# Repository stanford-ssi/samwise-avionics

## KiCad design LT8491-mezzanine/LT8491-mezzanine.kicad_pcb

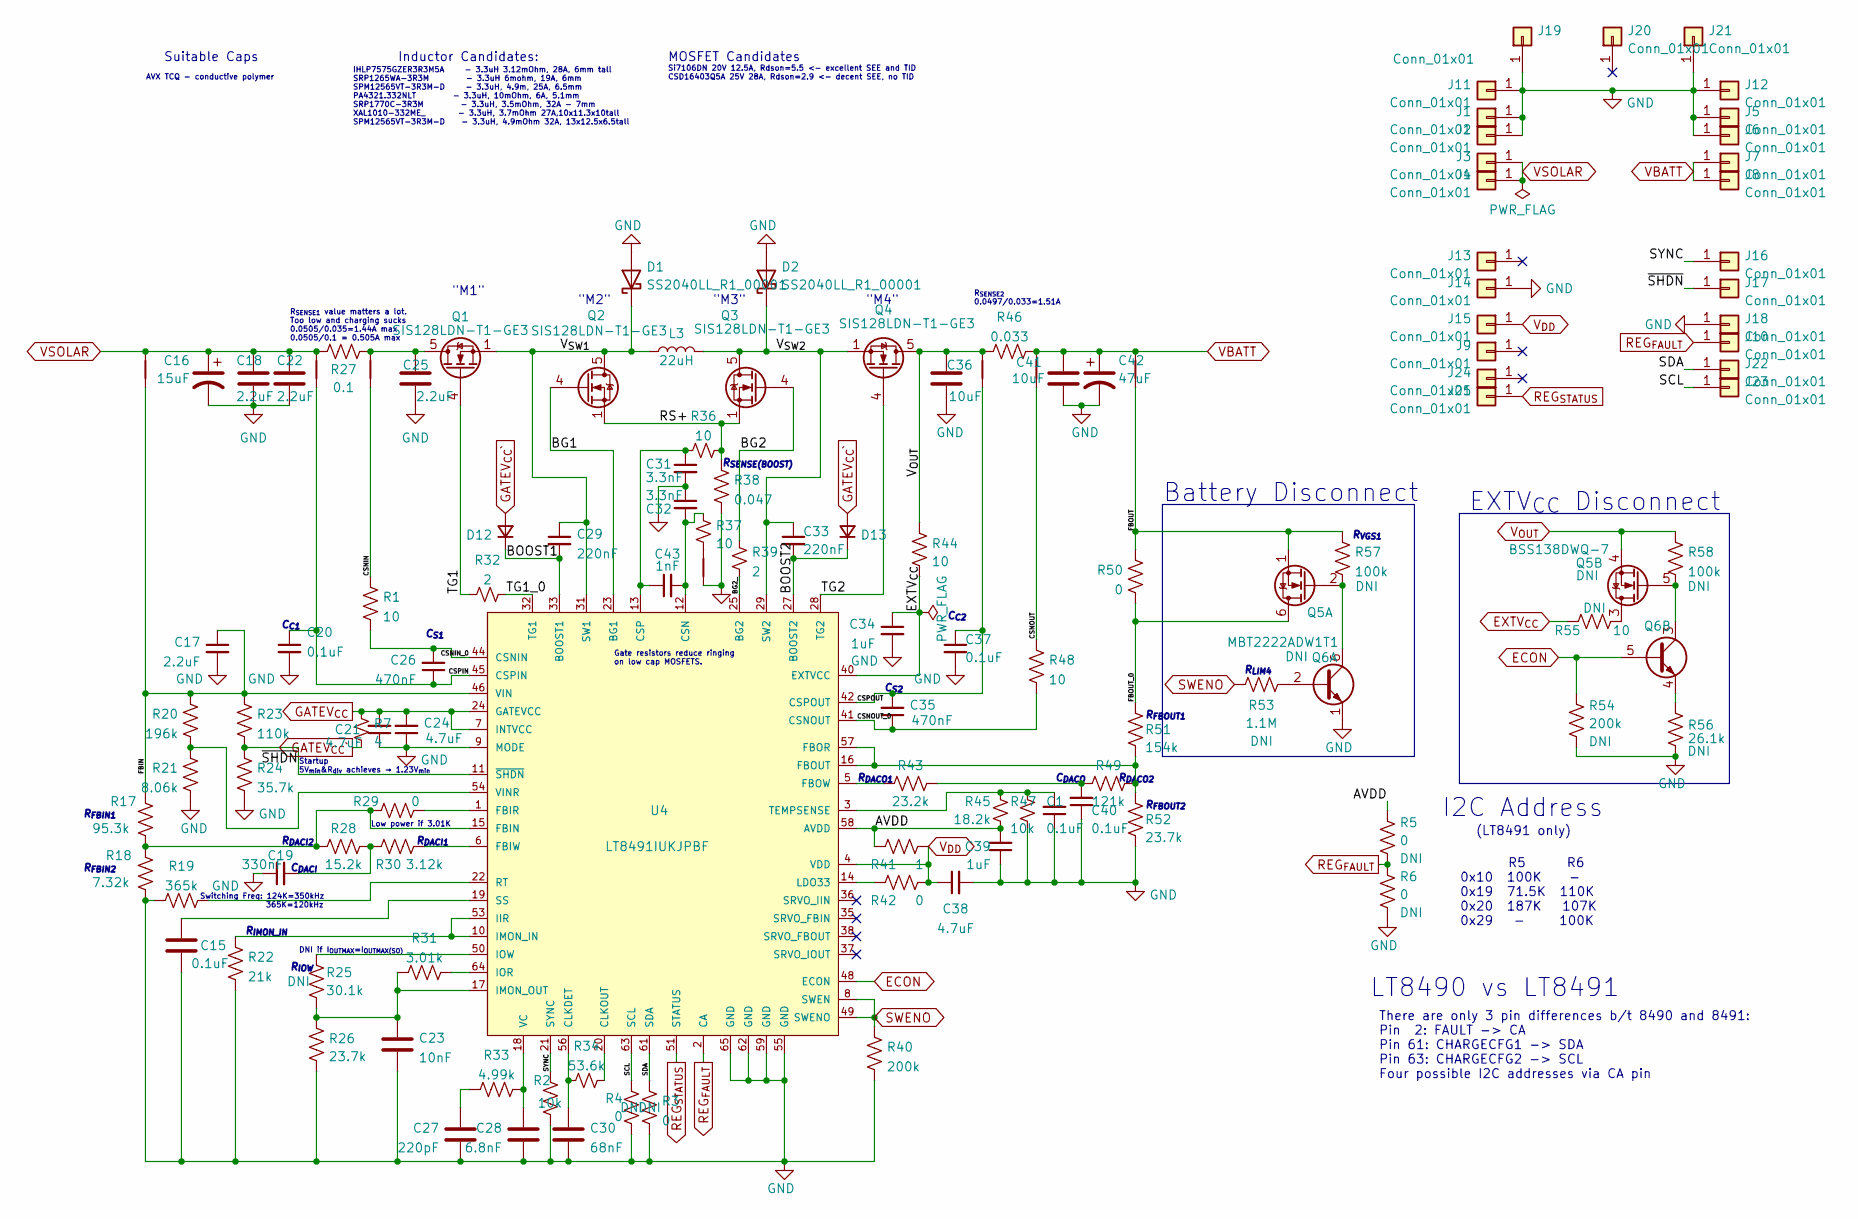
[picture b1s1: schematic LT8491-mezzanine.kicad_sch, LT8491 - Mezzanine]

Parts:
C1, C15, C20, C37, C40: 0.1uF; C_0603_1608Metric
C16: 15uF; CP_EIA-7343-30_AVX-N; Voltage 75V; Manufacturer_Part_Number TCQD336M016R0070E
C17, C18, C22, C25: 2.2uF; C_0805_2012Metric
C19: 330nF; C_0603_1608Metric
C21, C24, C38: 4.7uF; C_0603_1608Metric
C23: 10nF; C_0603_1608Metric
C26, C35: 470nF; C_0603_1608Metric
C27: 220pF; C_0603_1608Metric
C28: 6.8nF; C_0603_1608Metric
C29, C33: 220nF; C_0603_1608Metric
C30: 68nF; C_0603_1608Metric
C31, C32: 3.3nF; C_0603_1608Metric
C34, C39: 1uF; C_0603_1608Metric
C36, C41: 10uF; C_0805_2012Metric
C42: 47uF; CP_EIA-7343-30_AVX-N; Voltage 16V; Manufacturer_Part_Number TCQD476M016R0070E
C43: 1nF; C_0603_1608Metric
D1, D2: SS2040LL_R1_00001; D_PowerDI-123
D12, D13: CMMR1U-02 TR; D_SOD-123F
J1, J2, J3, J4, J5, J6, J7, J8, J9, J10, J11, J12, J13, J14, J15, J16, J17, J18, J19, J20, J21, J22, J23, J24, J25: Conn_01x01; mppt_castellation_05mm
L3: 22uH; L_SRP1770CC
NT1, NT2, NT3, NT4, NT5, NT6, NT7: NetTie_2; NetTie-2_SMD_Pad0.5mm
Q1, Q2, Q3, Q4: SIS128LDN-T1-GE3; Manufacturer_Part_Number SIS128LDN-T1-GE3
Q5: BSS138DWQ-7; Manufacturer_Part_Number BSS138DWQ-7; Mouser Part Number 621-BSS138DWQ-7
Q6: MBT2222ADW1T1; SOT-363_SC-70-6; Manufacturer_Part_Number MBT2222ADW1T1
R1, R36, R37, R44, R48, R55: 10; R_0603_1608Metric
R2, R47: 10k; R_0603_1608Metric
R3, R4, R5, R6, R29, R42, R50: 0; R_0603_1608Metric
R7: 4; R_0603_1608Metric
R17: 95.3k; R_0603_1608Metric
R18: 7.32k; R_0603_1608Metric
R19: 365k; R_0603_1608Metric
R20: 196k; R_0603_1608Metric
R21: 8.06k; R_0603_1608Metric
R22: 21k; R_0603_1608Metric
R23: 110k; R_0603_1608Metric
R24: 35.7k; R_0603_1608Metric
R25: 30.1k; R_0603_1608Metric
R26, R52: 23.7k; R_0603_1608Metric
R27: 0.1; R_1206_3216Metric
R28: 15.2k; R_0603_1608Metric
R30: 3.12k; R_0603_1608Metric
R31: 3.01k; R_0603_1608Metric
R32, R39: 2; R_0603_1608Metric
R33: 4.99k; R_0603_1608Metric
R34: 53.6k; R_0603_1608Metric
R38: 0.047; R_1206_3216Metric
R40, R54: 200k; R_0603_1608Metric
R41: 1; R_0603_1608Metric
R43: 23.2k; R_0603_1608Metric
R45: 18.2k; R_0603_1608Metric
R46: 0.033; R_1206_3216Metric
R49: 121k; R_0603_1608Metric
R51: 154k; R_0603_1608Metric
R53: 1.1M; R_0603_1608Metric
R56: 26.1k; R_0603_1608Metric
R57, R58: 100k; R_0603_1608Metric
U4: LT8491IUKJPBF; LT8491IUKJ#PBF

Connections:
/AVDD: C39.2, R5.1, R41.2, R45.2, U4.58 (AVDD)
/BG1: Q2.4 (G), U4.23 (BG1)
/BG2: Q3.4 (G), R39.1
/BG2_: R39.2, U4.25 (BG2)
/BOOST1: C29.2, D12.1 (K), U4.33 (BOOST1)
/BOOST2: C33.2, D13.1 (K), U4.27 (BOOST2)
/CSNIN: NT3.1, R1.1
/CSNIN_0: C26.2, R1.2, U4.44 (CSNIN)
/CSNOUT: NT5.1, R48.1
/CSNOUT_0: C35.1, R48.2, U4.41 (CSNOUT)
/CSPIN: C20.1, C26.1, NT2.1, U4.45 (CSPIN)
/CSPOUT: C35.2, C37.1, NT4.1, U4.42 (CSPOUT)
/EXTV_{CC}: C34.1, R44.2, R55.2, U4.40 (EXTVCC)
/FBIN: C17.1, NT6.1, R17.1, R20.1, R23.1, U4.46 (VIN)
/FBOUT: NT7.1, Q5.1 (S2), R50.1, R57.2
/FBOUT_0: Q5.6 (D1), R50.2, R51.1
/RS+: Q2.1 (S), Q2.2 (S), Q2.3 (S), Q3.1 (S), Q3.2 (S), Q3.3 (S), R36.1, R38.1
/SCL: J23.1, R4.1, U4.63 (SCL)
/SDA: J22.1, R3.1, U4.61 (SDA)
/SYNC: J16.1, R2.1, U4.21 (SYNC)
/TG1: Q1.4 (G), R32.2
/TG1_0: R32.1, U4.32 (TG1)
/TG2: Q4.4 (G), U4.28 (TG2)
/V_{OUT}: C36.1, NT4.2, Q4.5 (D), Q5.4 (S1), R44.1, R46.1, R58.2
/V_{SW1}: C29.1, D1.1 (K), L3.1, Q1.1 (S), Q1.2 (S), Q1.3 (S), Q2.5 (D), U4.31 (SW1)
/V_{SW2}: C33.1, D2.1 (K), L3.2, Q3.5 (D), Q4.1 (S), Q4.2 (S), Q4.3 (S), U4.29 (SW2)
/~SHDN: J17.1, R23.2, R24.1, U4.11 (~SHDN)
ECON: Q6.5 (B2), R54.1, U4.48 (ECON)
GATEV_{CC}: C21.2, C24.2, R7.2, U4.7 (INTVCC), U4.24 (GATEVCC)
GATEV_{CC}`: D12.2 (A), D13.2 (A), R7.1
GND: C1.1, C15.2, C16.2, C17.2, C18.2, C19.1, C20.2, C21.1, C22.2, C23.2, C24.1, C25.2, C27.2, C28.1, C30.2, C31.2, C32.1, C34.2, C36.2, C37.2, C38.2, C39.1, C40.1, C41.2, C42.2, D1.2 (A), D2.2 (A), J1.1, J2.1, J5.1, J6.1, J11.1, J12.1, J14.1, J18.1, J19.1, J21.1, NT1.1, Q6.1 (E1), R2.2, R3.2, R4.2, R6.2, R18.2, R19.2, R21.2, R22.2, R24.2, R26.2, R38.2, R40.2, R47.1, R52.2, R54.2, R56.1, U4.9 (MODE), U4.55 (GND), U4.59 (GND), U4.62 (GND), U4.65 (GND)
unnamed: C19.2, R28.1, R30.2
unnamed: C27.1, R33.1
unnamed: C40.2, R43.1, R49.2
unnamed: NT1.2, R37.2
unnamed: C25.1, NT3.2, Q1.5 (D), R27.2
unnamed: Q5.2 (G2), Q6.6 (C1), R57.1
unnamed: Q5.3 (D2), R55.1
unnamed: Q5.5 (G1), Q6.3 (C2), R58.1
unnamed: Q6.2 (B1), R53.2
unnamed: Q6.4 (E2), R56.2
unnamed: C30.1, R34.1, U4.56 (CLKDET)
unnamed: R34.2, U4.20 (CLKOUT)
unnamed: C32.2, C43.2, R37.1, U4.12 (CSN)
unnamed: C31.1, C43.1, R36.2, U4.13 (CSP)
unnamed: R17.2, R18.1, R28.2, R29.2, U4.15 (FBIN)
unnamed: R29.1, U4.1 (FBIR)
unnamed: R30.1, U4.6 (FBIW)
unnamed: R49.1, R51.2, R52.1, U4.16 (FBOUT), U4.57 (FBOR)
unnamed: R43.2, U4.5 (FBOW)
unnamed: R22.1, U4.10 (IMON_IN), U4.53 (IIR)
unnamed: C23.1, R25.2, R26.1, R31.2, U4.17 (IMON_OUT)
unnamed: R31.1, U4.64 (IOR)
unnamed: R25.1, U4.50 (IOW)
unnamed: R42.2, U4.14 (LDO33)
unnamed: R19.1, U4.22 (RT)
unnamed: C15.1, U4.19 (SS)
unnamed: C1.2, R45.1, R47.2, U4.3 (TEMPSENSE)
unnamed: C28.2, R33.2, U4.18 (VC)
unnamed: R20.2, R21.1, U4.54 (VINR)
REG_{FAULT}: J10.1, R5.2, R6.1, U4.2 (CA)
REG_{STATUS}: J25.1, U4.51 (STATUS)
SWENO: R40.1, R53.1, U4.8 (SWEN), U4.49 (SWENO)
VBATT: C41.1, C42.1, J7.1, J8.1, NT5.2, NT7.2, R46.2
VSOLAR: C16.1, C18.1, C22.1, J3.1, J4.1, NT2.2, NT6.2, R27.1
V_{DD}: C38.1, J15.1, R41.1, R42.1, U4.4 (VDD)

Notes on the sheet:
R_{DACI1}
C_{DACO}
C_{C2}
DNI if I_{OUTMAX}=I_{OUTMAX(SO)}
Battery Disconnect
R_{IMON_IN}
Startup 5V_{min}&R_{div} achieves → 1.23V_{min}
C_{S1}
C_{S2}
Switching Freq: 124K=350kHz 365K=120kHz
Suitable Caps
R_{LIM4}
"M4"
Gate resistors reduce ringing on low cap MOSFETS.
R_{DACO2}
Si7106DN 20V 12.5A, Rdson=5.5 <- excellent SEE and TID CSD16403Q5A 25V 28A, Rdson=2.9 <- decent SEE, no TID
There are only 3 pin differences b/t 8490 and 8491: Pin 2: FAULT -> CA Pin 61: CHARGECFG1 -> SDA Pin 63: CHARGECFG2 -> SCL Four possible I2C addresses via CA pin
R_{DACI2}
R_{SENSE(BOOST)}
R_{FBIN2}
C_{C1}
R_{DACO1}
R5 R6 0x10 100K - 0x19 71.5K 110K 0x20 187K 107K 0x29 - 100K
IHLP7575GZER3R3M5A - 3.3uH 3.12mOhm, 28A, 6mm tall SRP1265WA-3R3M - 3.3uH 6mohm, 19A, 6mm SPM12565VT-3R3M-D - 3.3uH, 4.9m, 25A, 6.5mm PA4321.332NLT - 3.3uH, 10mOhm, 6A, 5.1mm SRP1770C-3R3M - 3.3uH, 3.5mOhm, 32A - 7mm XAL1010-332ME_ - 3.3uH, 3.7mOhm 27A,10x11.3x10tall SPM12565VT-3R3M-D - 3.3uH, 4.9m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
R_{SENSE1} value matters a lot. Too low and charging sucks 0.0505/0.035=1.44A max 0.0505/0.1 = 0.505A max
EXTV_{CC} Disconnect
"M2"
"M3"
R_{FBIN1}
R_{IOW}
(LT8491 only)
MOSFET Candidates
AVX TCQ - conductive polymer
C_{DACI}
"M1"
R_{FBOUT2}
Inductor Candidates:
R_{FBOUT1}
R_{SENSE2} 0.0497/0.033=1.51A
LT8490 vs LT8491

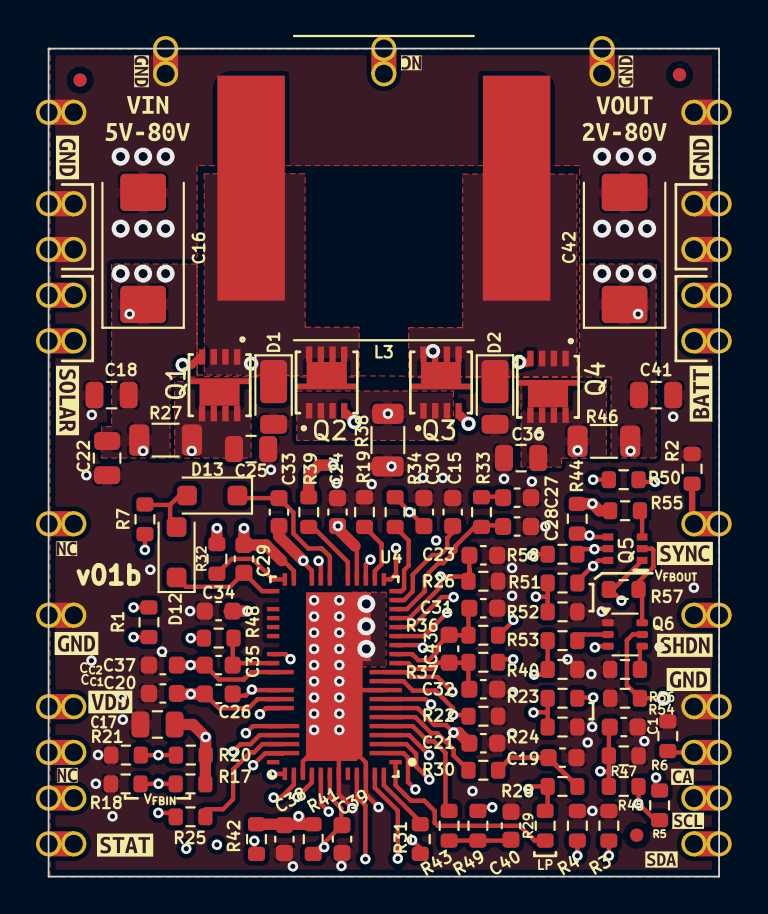
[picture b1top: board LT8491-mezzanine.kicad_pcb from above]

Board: 6 copper layers, 37.2 x 46.0 mm, 145 parts (0 on the bottom side), 66 nets.

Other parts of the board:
Ref**: Val**; holliday
kibuzzard-62D49DAC, kibuzzard-62D49DAC#2, kibuzzard-62D49DAC#3: G***; kibuzzard-62D49DAC
kibuzzard-62D49DF0, kibuzzard-62D49DF0#2: G***; kibuzzard-62D49DF0
kibuzzard-623CC1D5, kibuzzard-623CC1D5#2, kibuzzard-623CC1D5#3, kibuzzard-623CC1D5#4: G***; kibuzzard-623CC1D5
kibuzzard-623CC1F4: G***; kibuzzard-623CC1F4
kibuzzard-623CC3F2: G***; kibuzzard-623CC3F2
kibuzzard-623CC9B2: G***; kibuzzard-623CC9B2
kibuzzard-623CC23C: G***; kibuzzard-623CC23C
kibuzzard-623CCAD0: G***; kibuzzard-623CCAD0
kibuzzard-623CCAFA: G***; kibuzzard-623CCAFA
kibuzzard-623CCB0B: G***; kibuzzard-623CCB0B
kibuzzard-623CCB15: G***; kibuzzard-623CCB15
kibuzzard-623CCD34: G***; kibuzzard-623CCD34
kibuzzard-623DE3C4: G***; kibuzzard-623DE3C4
kibuzzard-623E06E1: G***; kibuzzard-623E06E1
kibuzzard-623E06ED: G***; kibuzzard-623E06ED
kibuzzard-623E06FB: G***; kibuzzard-623E06FB

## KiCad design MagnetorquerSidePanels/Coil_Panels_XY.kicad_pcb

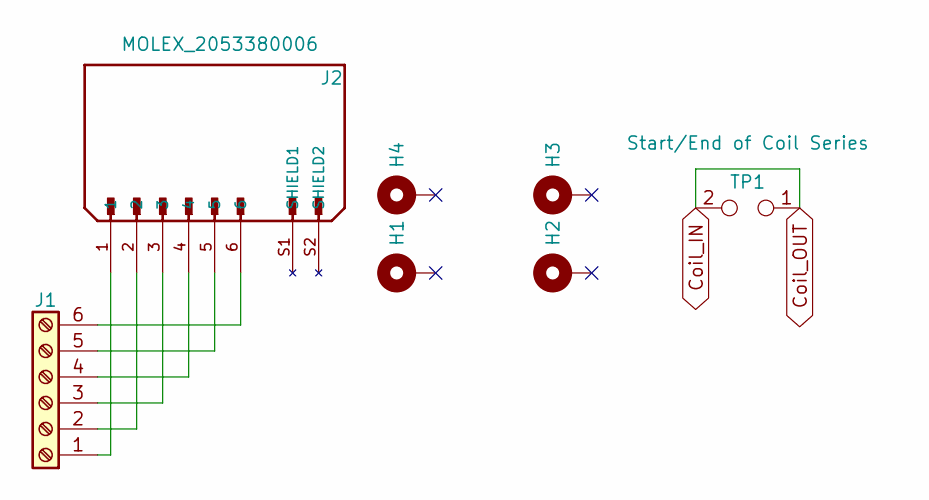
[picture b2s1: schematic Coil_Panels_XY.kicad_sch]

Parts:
H1, H2, H3, H4: MountingHole_2.2mm_M2_DIN965_Pad_TopBottom
J1: Through_Hole_1; PinHeader_1x06_P2.54mm_Vertical
J2: MOLEX_2053380006
TP1: Start/End of Coil Series; TestPointConnection

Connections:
Coil_IN: TP1.1, TP1.2
unnamed: J1.1, J2.1
unnamed: J1.2, J2.2
unnamed: J1.3, J2.3
unnamed: J1.4, J2.4
unnamed: J1.5, J2.5
unnamed: J1.6, J2.6

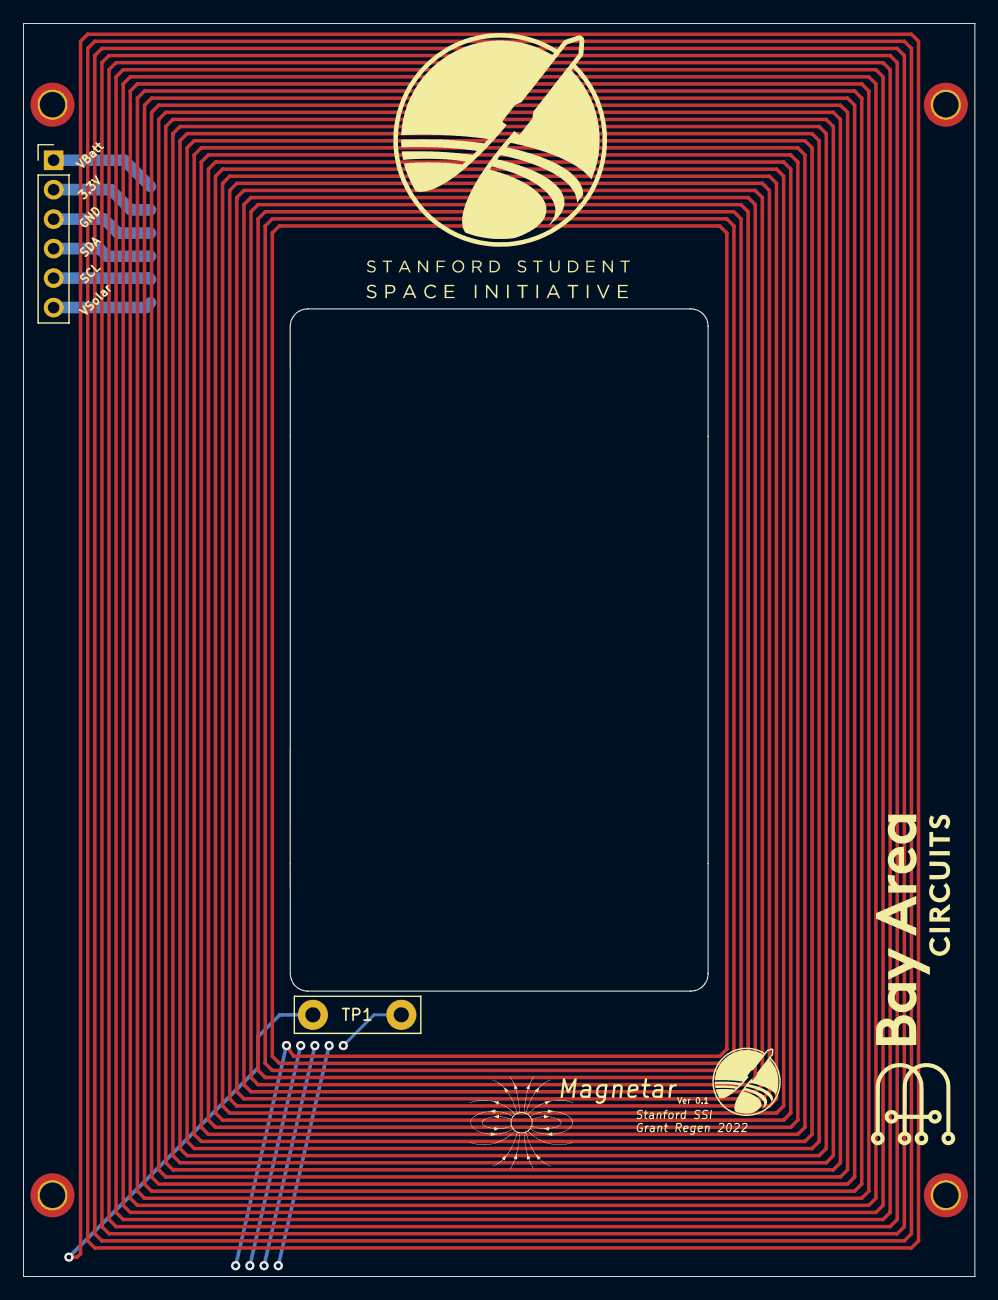
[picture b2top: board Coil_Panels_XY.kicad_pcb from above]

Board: 6 copper layers, 82.0 x 108.0 mm, 7 parts (1 on the bottom side), 7 nets.

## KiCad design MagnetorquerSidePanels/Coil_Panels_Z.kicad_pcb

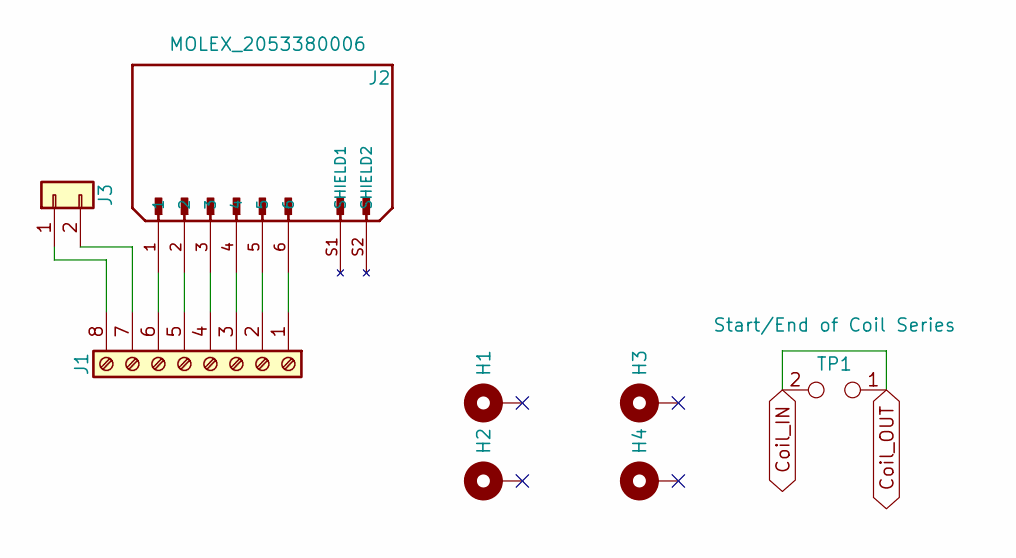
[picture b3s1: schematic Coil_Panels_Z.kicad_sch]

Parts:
H1, H2, H3, H4: MountingHole_2.2mm_M2_DIN965_Pad_TopBottom
J1: Screw_Terminal_01x08; PinHeader_1x08_P2.54mm_Vertical
J2: MOLEX_2053380006
J3: Conn_01x02; 2053380002
TP1: Start/End of Coil Series; TestPointConnection

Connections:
Coil_IN: TP1.1, TP1.2
unnamed: J1.1, J2.6
unnamed: J1.2, J2.5
unnamed: J1.3, J2.4
unnamed: J1.4, J2.3
unnamed: J1.5, J2.2
unnamed: J1.6, J2.1
unnamed: J1.7, J3.2
unnamed: J1.8, J3.1

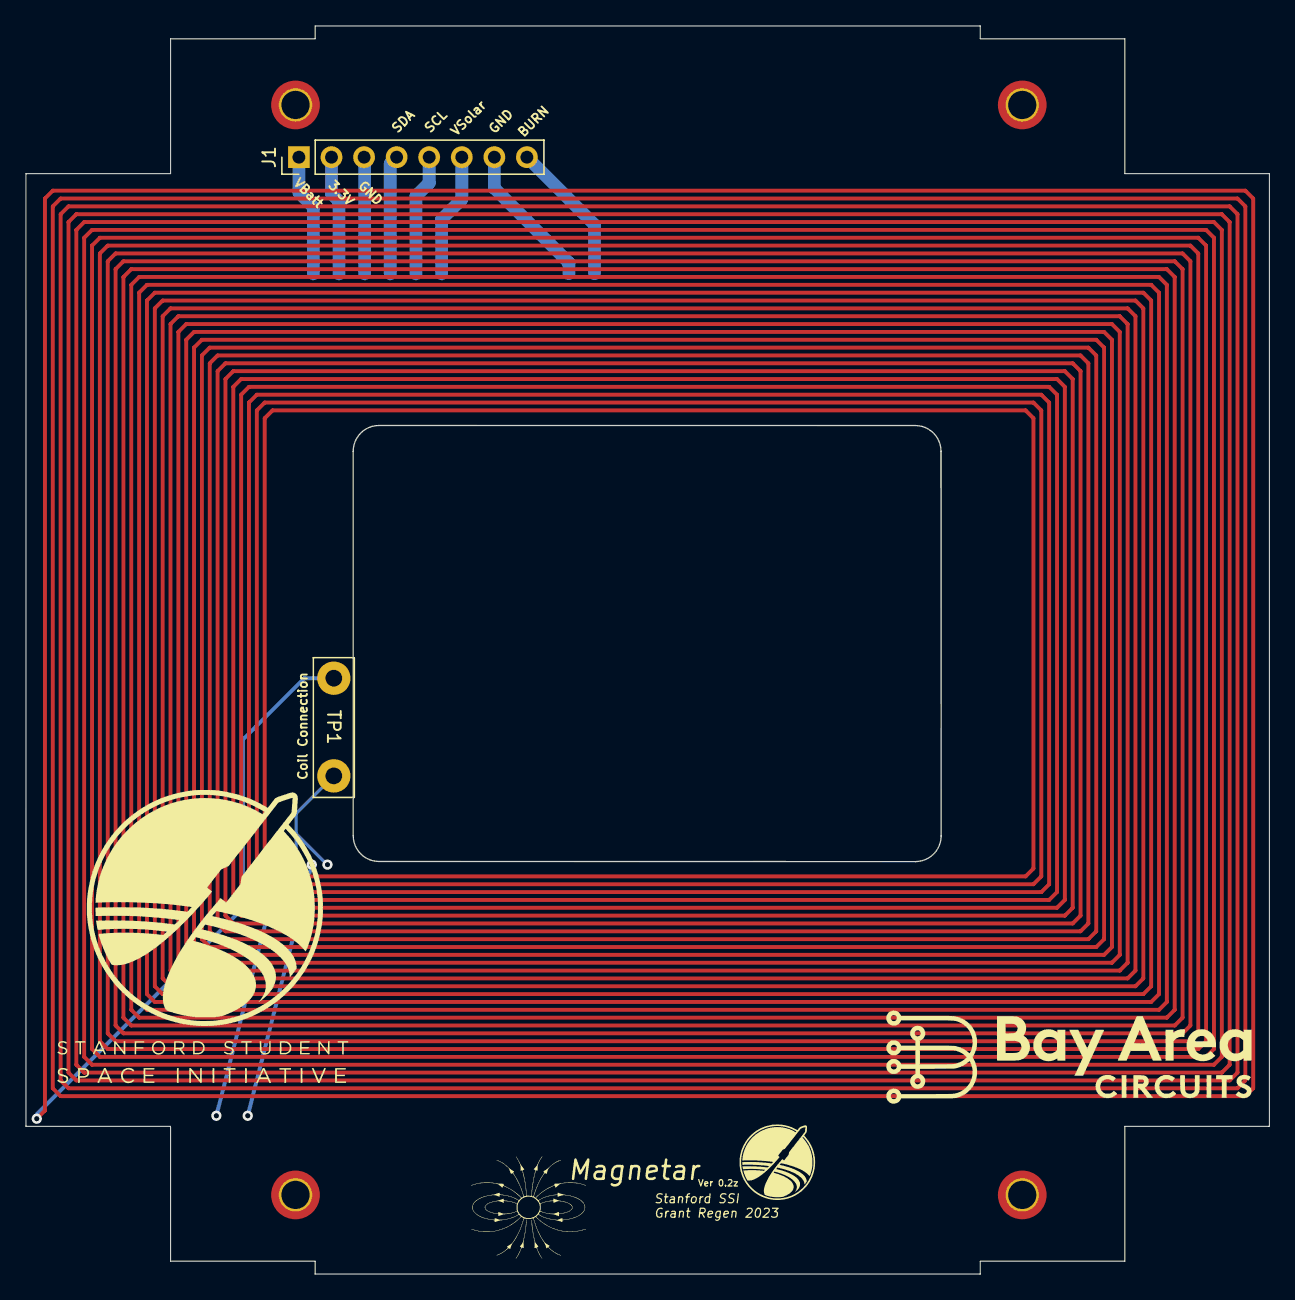
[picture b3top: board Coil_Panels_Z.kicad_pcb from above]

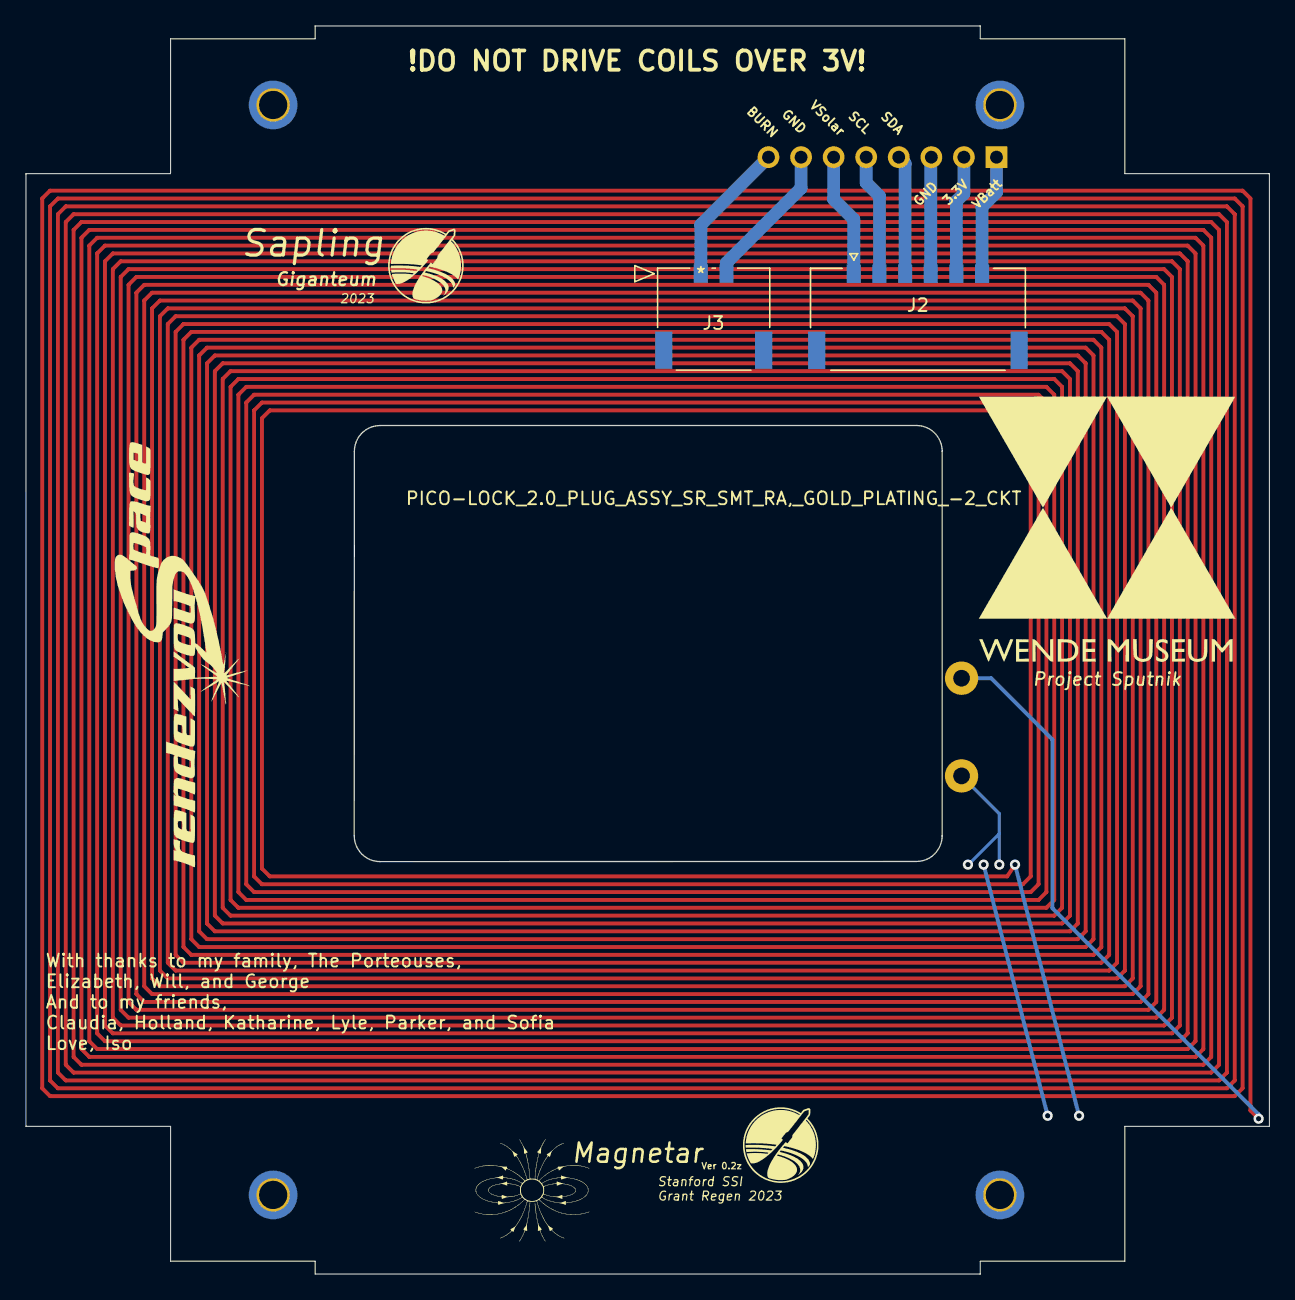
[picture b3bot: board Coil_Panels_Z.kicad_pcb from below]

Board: 6 copper layers, 97.0 x 97.3 mm, 8 parts (2 on the bottom side), 9 nets.

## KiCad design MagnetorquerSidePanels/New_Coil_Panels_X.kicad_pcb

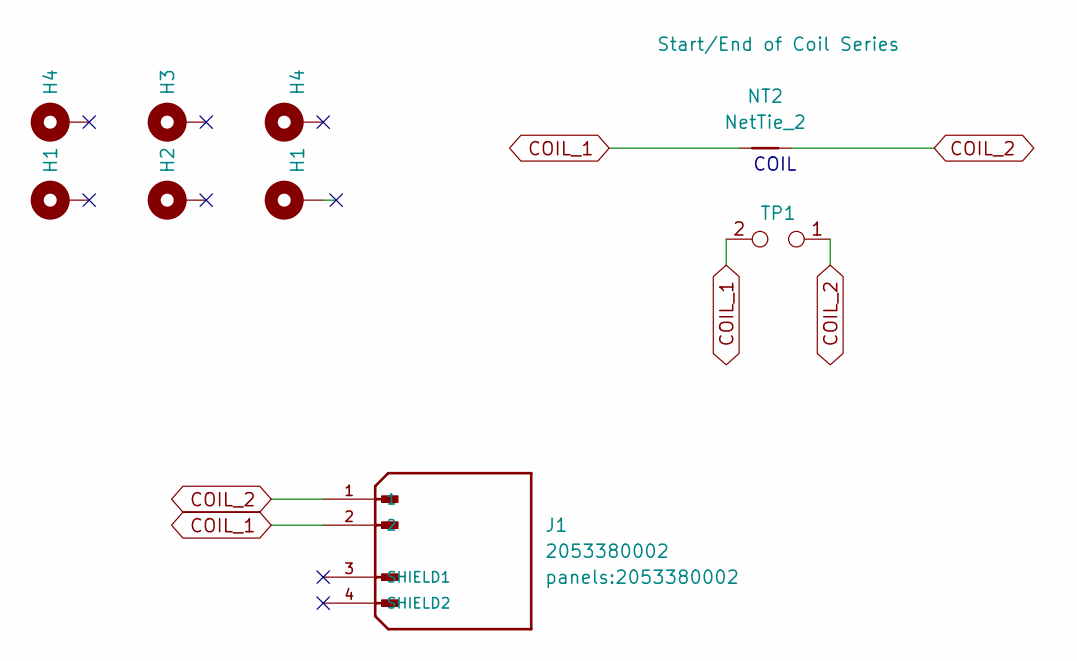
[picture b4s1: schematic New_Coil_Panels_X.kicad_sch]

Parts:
H1, H2, H3, H4: MountingHole_2.2mm_M2_DIN965_Pad_TopBottom
J1: 2053380002; PARTREV B
NT2: NetTie_2; NetTie-2_SMD_Pad0.5mm
TP1: Start/End of Coil Series; TestPointConnection

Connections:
COIL_1: J1.2, NT2.1, TP1.2
COIL_2: J1.1, NT2.2, TP1.1

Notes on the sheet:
COIL

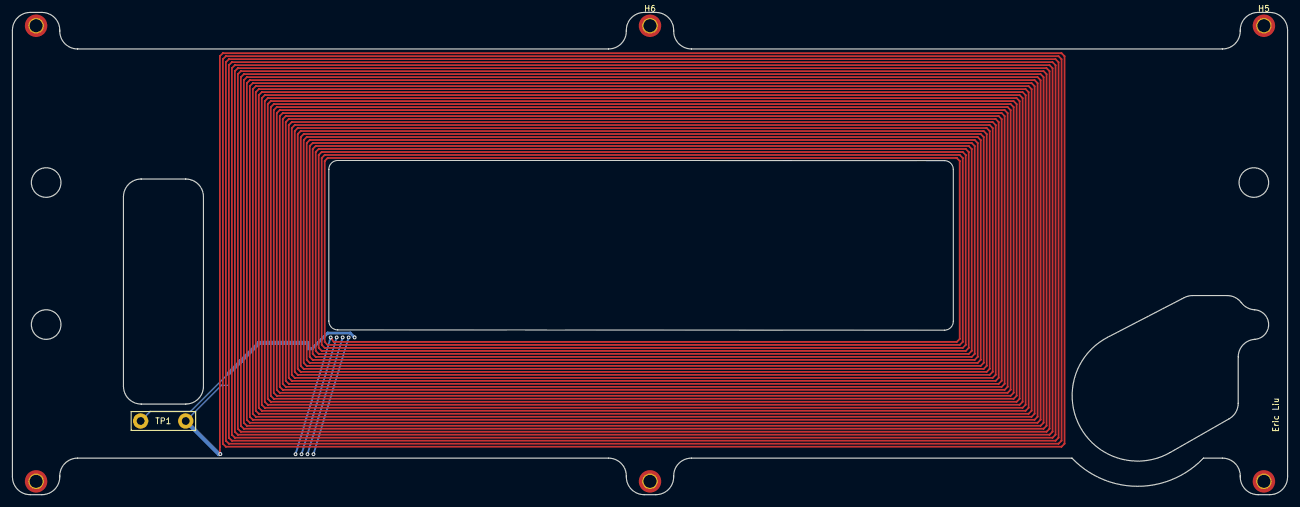
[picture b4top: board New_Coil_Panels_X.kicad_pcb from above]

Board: 6 copper layers, 215.5 x 81.5 mm, 9 parts (1 on the bottom side), 2 nets.

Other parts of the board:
H5, H6: MountingHole_2.2mm_M2_DIN965_Pad_TopBottom

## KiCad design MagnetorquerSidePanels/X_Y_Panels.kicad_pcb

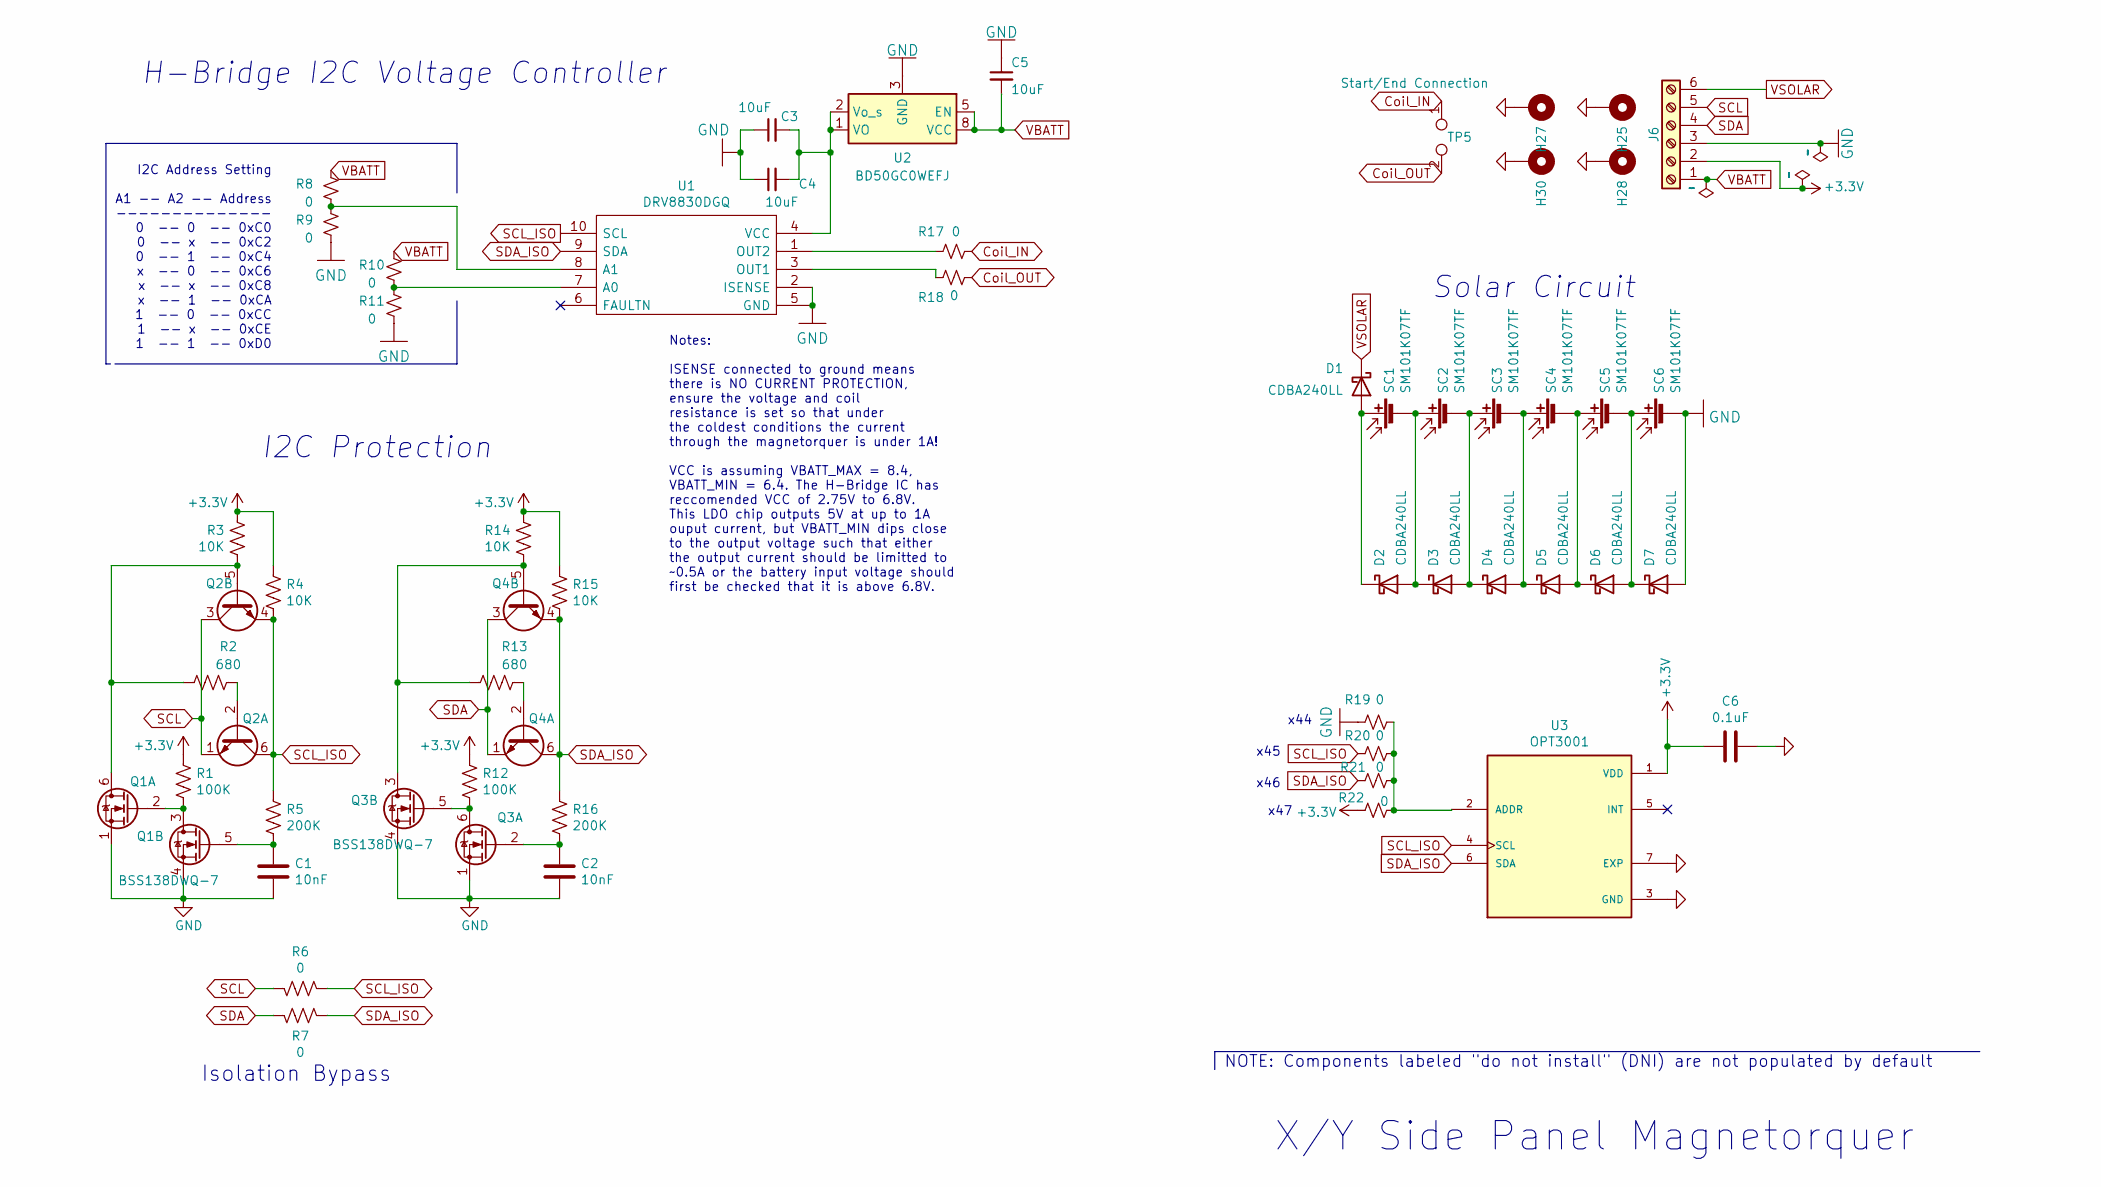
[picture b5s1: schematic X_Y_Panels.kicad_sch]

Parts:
C1, C2: 10nF; C_0603_1608Metric
C3, C4, C5: 10uF; C_1206_3216Metric
C6: 0.1uF; C_0603_1608Metric
D1, D2, D3, D4, D5, D6, D7: CDBA240LL; DO-214AC
H25, H27, H28, H30: MountingHole_2.2mm_M2_DIN965_Pad_TopBottom
J6: Through_Hole_1; PinHeader_1x06_P2.54mm_Vertical
Q1, Q3: BSS138DWQ-7; Manufacturer_Part_Number BSS138DWQ-7; Mouser Part Number 621-BSS138DWQ-7
Q2, Q4: MBT2222ADW1T1; SOT-363_SC-70-6
R1, R12: 100K; R_0603_1608Metric
R2, R13: 680; R_0603_1608Metric
R3, R4, R14, R15: 10K; R_0603_1608Metric
R5, R16: 200K; R_0603_1608Metric
R6, R7, R8, R9, R10, R11, R17, R18, R19, R20, R21, R22: 0; R_0603_1608Metric
SC1, SC2, SC3, SC4, SC5, SC6: SM101K07TF
TP5: Start/End Connection; TestPointConnection
U1: DRV8830DGQ; Manufacturer_Part_Number DRV8830DGQR; Mouser Part Number 595-DRV8830DGQR
U2: BD50GC0WEFJ; HTSOP-8-1EP_3.9x4.9mm_P1.27mm_EP2.4x3.2mm
U3: OPT3001

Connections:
+3V3: C6.1, J6.2, R1.2, R3.1, R4.2, R12.2, R14.1, R15.2, R22.1, U3.1 (VDD)
Coil_IN: R17.2, TP5.1
Coil_OUT: R18.2, TP5.2
unnamed: D1.2 (A), D2.1 (K), SC1.1 (+)
unnamed: D2.2 (A), D3.1 (K), SC1.2 (-), SC2.1 (+)
unnamed: D3.2 (A), D4.1 (K), SC2.2 (-), SC3.1 (+)
unnamed: D4.2 (A), D5.1 (K), SC3.2 (-), SC4.1 (+)
unnamed: D5.2 (A), D6.1 (K), SC4.2 (-), SC5.1 (+)
unnamed: D6.2 (A), D7.1 (K), SC5.2 (-), SC6.1 (+)
unnamed: Q1.6 (D1), Q2.5 (B2), R2.1, R3.2
unnamed: Q1.2 (G2), Q1.3 (D2), R1.1
unnamed: C1.1, Q1.5 (G1), R5.1
unnamed: Q2.2 (B1), R2.2
unnamed: Q3.5 (G1), Q3.6 (D1), R12.1
unnamed: C2.1, Q3.2 (G2), R16.1
unnamed: Q3.3 (D2), Q4.5 (B2), R13.2, R14.2
unnamed: Q4.2 (B1), R13.1
unnamed: R10.2, R11.1, U1.7 (A0)
unnamed: R8.2, R9.1, U1.8 (A1)
unnamed: R18.1, U1.3 (OUT1)
unnamed: R17.1, U1.1 (OUT2)
unnamed: C3.2, C4.2, U1.4 (VCC), U2.1 (VO), U2.2 (Vo_s)
unnamed: R19.2, R20.2, R21.2, R22.2, U3.2 (ADDR)
SCL: J6.5, Q2.1 (E1), Q2.3 (C2), R6.1
SCL_ISO: Q2.4 (E2), Q2.6 (C1), R4.1, R5.2, R6.2, R20.1, U1.10 (SCL), U3.4 (SCL)
SDA: J6.4, Q4.1 (E1), Q4.3 (C2), R7.1
SDA_ISO: Q4.4 (E2), Q4.6 (C1), R7.2, R15.1, R16.2, R21.1, U1.9 (SDA), U3.6 (SDA)
VBATT: C5.2, J6.1, R8.1, R10.1, U2.5 (EN), U2.8 (VCC)
VSOLAR: D1.1 (K), J6.6

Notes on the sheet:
x47
I2C Protection
H-Bridge I2C Voltage Controller
Isolation Bypass
x44
Notes: ISENSE connected to ground means there is NO CURRENT PROTECTION, ensure the voltage and coil resistance is set so that under the coldest conditions the current through the magnetorquer is under 1A! VCC is assuming VBATT_MAX = 8.4, VBATT_MIN = 6.4. The H-Bridge IC has reccomended VCC of 2.75V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
X/Y Side Panel Magnetorquer
x46
NOTE: Components labeled "do not install" (DNI) are not populated by default
x45
I2C Address Setting A1 -- A2 -- Address -------------- 0 -- 0 -- 0xC0 0 -- x -- 0xC2 0 -- 1 -- 0xC4 x -- 0 -- 0xC6 x -- x -- 0xC8 x -- 1 -- 0xCA 1 -- 0 -- 0xCC 1 -- x -- 0xCE 1 -- 1 -- 0xD0
Solar Circuit

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
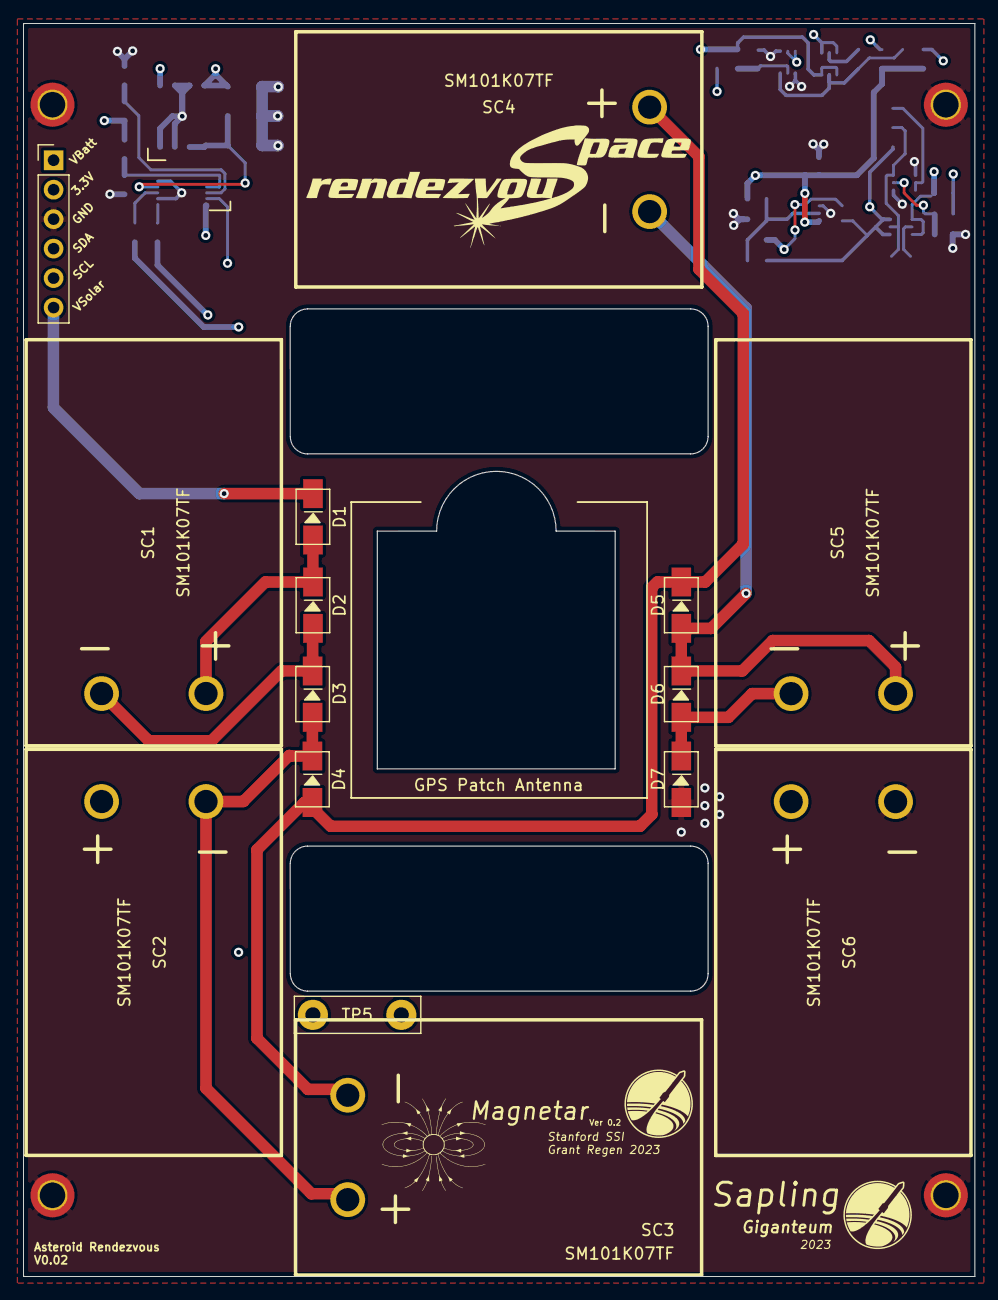
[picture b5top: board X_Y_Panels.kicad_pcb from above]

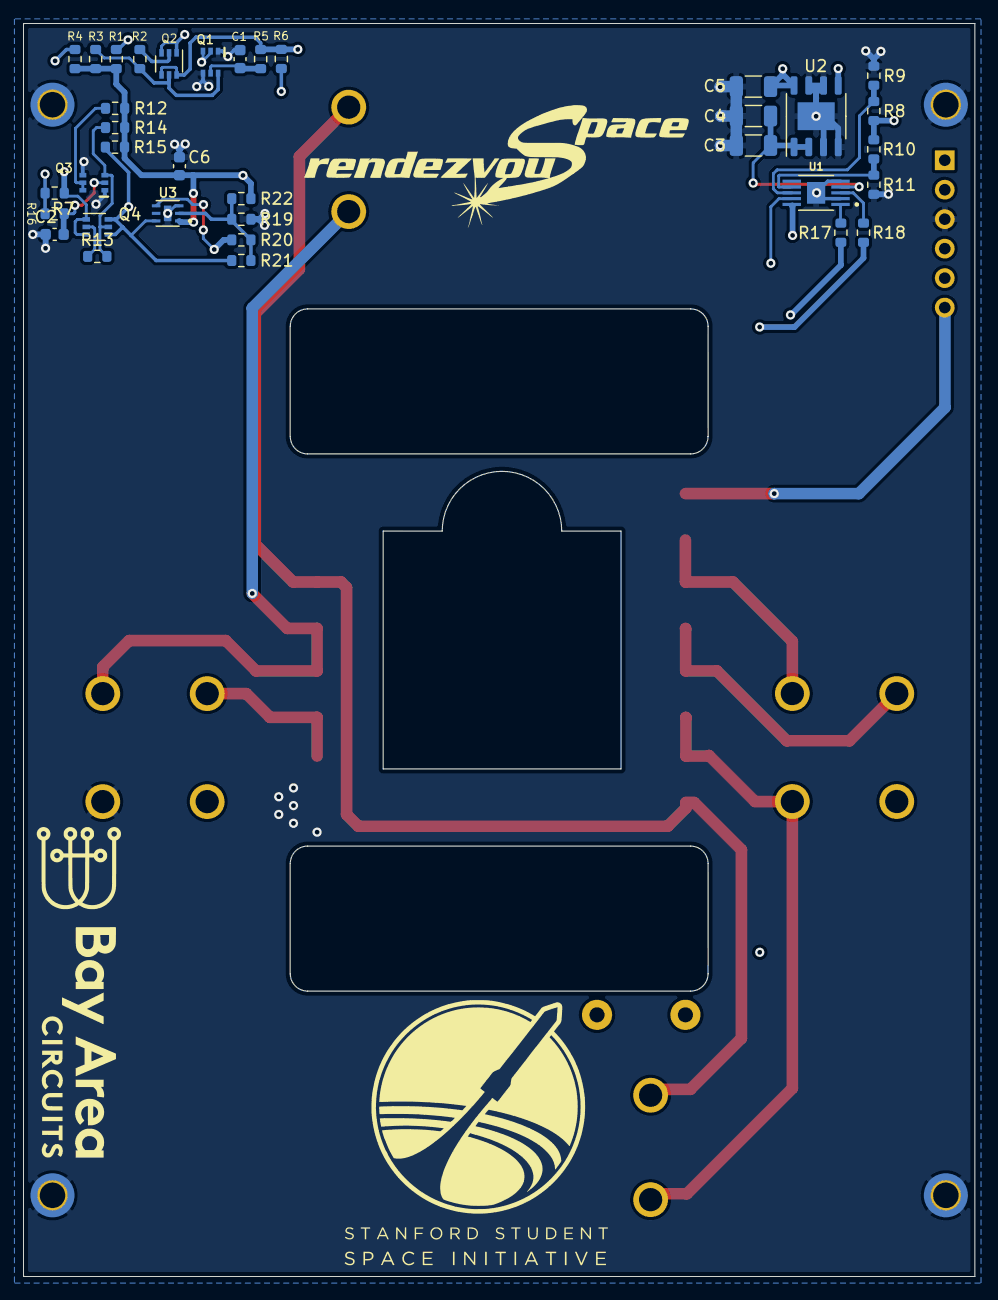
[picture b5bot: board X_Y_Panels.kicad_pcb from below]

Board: 6 copper layers, 82.0 x 108.0 mm, 54 parts (35 on the bottom side), 30 nets.

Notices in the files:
parts and their libraries:
Copyright 2021 Accelerated Designs. All rights reserved.
